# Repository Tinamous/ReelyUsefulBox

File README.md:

Reely Useful Box - SMD Reel storage and dispenser.
==================================================

SMD reel storage and dispenser based on a Really Useful Storage Box.

Each reel is held and dispensed individually.
The box will hold 25 individual reels (assuming standard 8mm tape for resistors/capacitors).
Each reel holder is 13mm wide. For wider tape/reels this could be doubled to keep to the same hole grid.
Each reel holder is made of 3 different printed parts (1x Top dispenser, 1x reel holder top, 2x reel arms).
Component counter option with LED and photodiode counting of the tape holes.

You can have as few as you want, or as many (well 25 per box and as many boxes as you need).

All design files are Openscad and .stl for direct printing. I found it best to print with a brim as these are long parts and have a tendency to warp at the ends.

##MountingPlate

This is the drilling guide. You can either print it out and drill, or laser cut some acrylic with it.

* Open the .svg file in Inkscape and print this out. 
* It's bigger than A4/Letter, do not scale it! (The box is bigger than A4 length ways so you will need a couple of these for the full 25 way box).
* Stick the sheet to the box lid, allow a margin of about 4mm around the edges where the lid inner curves up (remember the reel holder top has to fit inside).
* Ensure the holes line up with the Dispenser.
* Drill the holes. 
** 4MM for the M3 screw holes (4x).
** 5mm for the LED insert.
** 9-10mm for the square tape hole. This is likely to crack the lid in the process, maybe drill 4 M3.5 holes at each corner and cut, or cut out the entire length of all the sections with a dremel of something  (Be VERY careful if you use a knife, the lid is very tough!).

##Dispenser

This sits on the top of the lid. 

Print in any color you like, you can color code the dispensers to match your components. I'm using:

* 1206 Resistors: Red
* 0805 Resistors: Green
* 1206 Capacitors: White
* 0805 Capacitors: Grey
* 1206 LEDs (Blue): Blue
* Other: Bronze

Original inspiration taken from http://www.thingiverse.com/thing:1080195 with modifications.

* Print this on it's side without supports but with a brim.
* 4 mounting holes for M3 countersunk machine screws.
* A small hole that aligns with the holes in the tape and accepts a 3mm LED underneath.
* The tape film wraps around the block on the top and exits vertically, so pulling the tape film up advances the tape and removes the film.
* Of you can just leave the film on if you want to cut of a section of tape.
* The top block has a hold in the back. Use a M3 heatfit   insert in here if you want to use the component usage sensor block.

## ReelHolder-Top (ReelHolder.scad/ReelHolder.stl)

This sits inside the box to hold the reel arms and is screwed to the lid with the dispenser on the top.

* Print without supports but with a brim as this tends to warp at the edges.
* Fit 3x or 4x M3 HeatFit inserts (Do not fit the one by the square cut out if you wish to use the ComponentUsageSensor block.
* The M5 hole allows a 3mm LED to be pushed through into the dispenser 

## ReelHolder-Arm

These hold the reel and is mounted in the ReelHolder-Top.

* Print 2x of these for each arm.
* These push together either side of the reel and the ReelHolder-Top
* For the end ones you may wish to use a M3 HeatFit insert and small machine screw to hold the tops together if you don't have a tight fit.
* If the arms are not a good fit together change the value of cyinderMatingTollerance in the OpenScad file. I found 0.4 worked well, 0.2 was very tight.
* You may also like to shorten these arms. The variable armHeight sets the length of these. 150mm should allow the reel to be pulled to one side to be replaced.

## Parts Required:

* M3 Heatfit insert Part 1010655 http://www.insertsdirect.com/cgi-bin/sh000001.cgi?WD=1010655&PN=unheaded-heatfit-insert%2ehtml#a1010655
* M3 x 20mm countersunk machine screw (x5 per reel)
* M3 x 6mm countersunk machine screw (x1 for end reels only, or x2 per reel if you need to keep the reel arms together).
* 19XL Really Useful Box http://www.ryman.co.uk/really-useful-storage-box-19xl-litre
* PLA.
* Drills: 4mm, 5mm, 9 or 10mm.
* SMD devices on reels!

## Printer Settings

* Printer: Ultimaker 2 Extended+
* Print Sequence: One at a Time
* Profile: Fast print
** Layer Height: 0.15
** Infil: 20%
** Speed: 60 mm/s
** Wall Thickness: 0.7mm
** Top/Bottom Thickness: 0.75mm
* Build Plate Adhesion: Brim
* Support: None

## Electronics

The dispenser is designed to have a LED/PhotoTransistor pair either side of the tape to count the holes in the tape as they pass. See PCB folder for
instructions on the counter and LED PCB.

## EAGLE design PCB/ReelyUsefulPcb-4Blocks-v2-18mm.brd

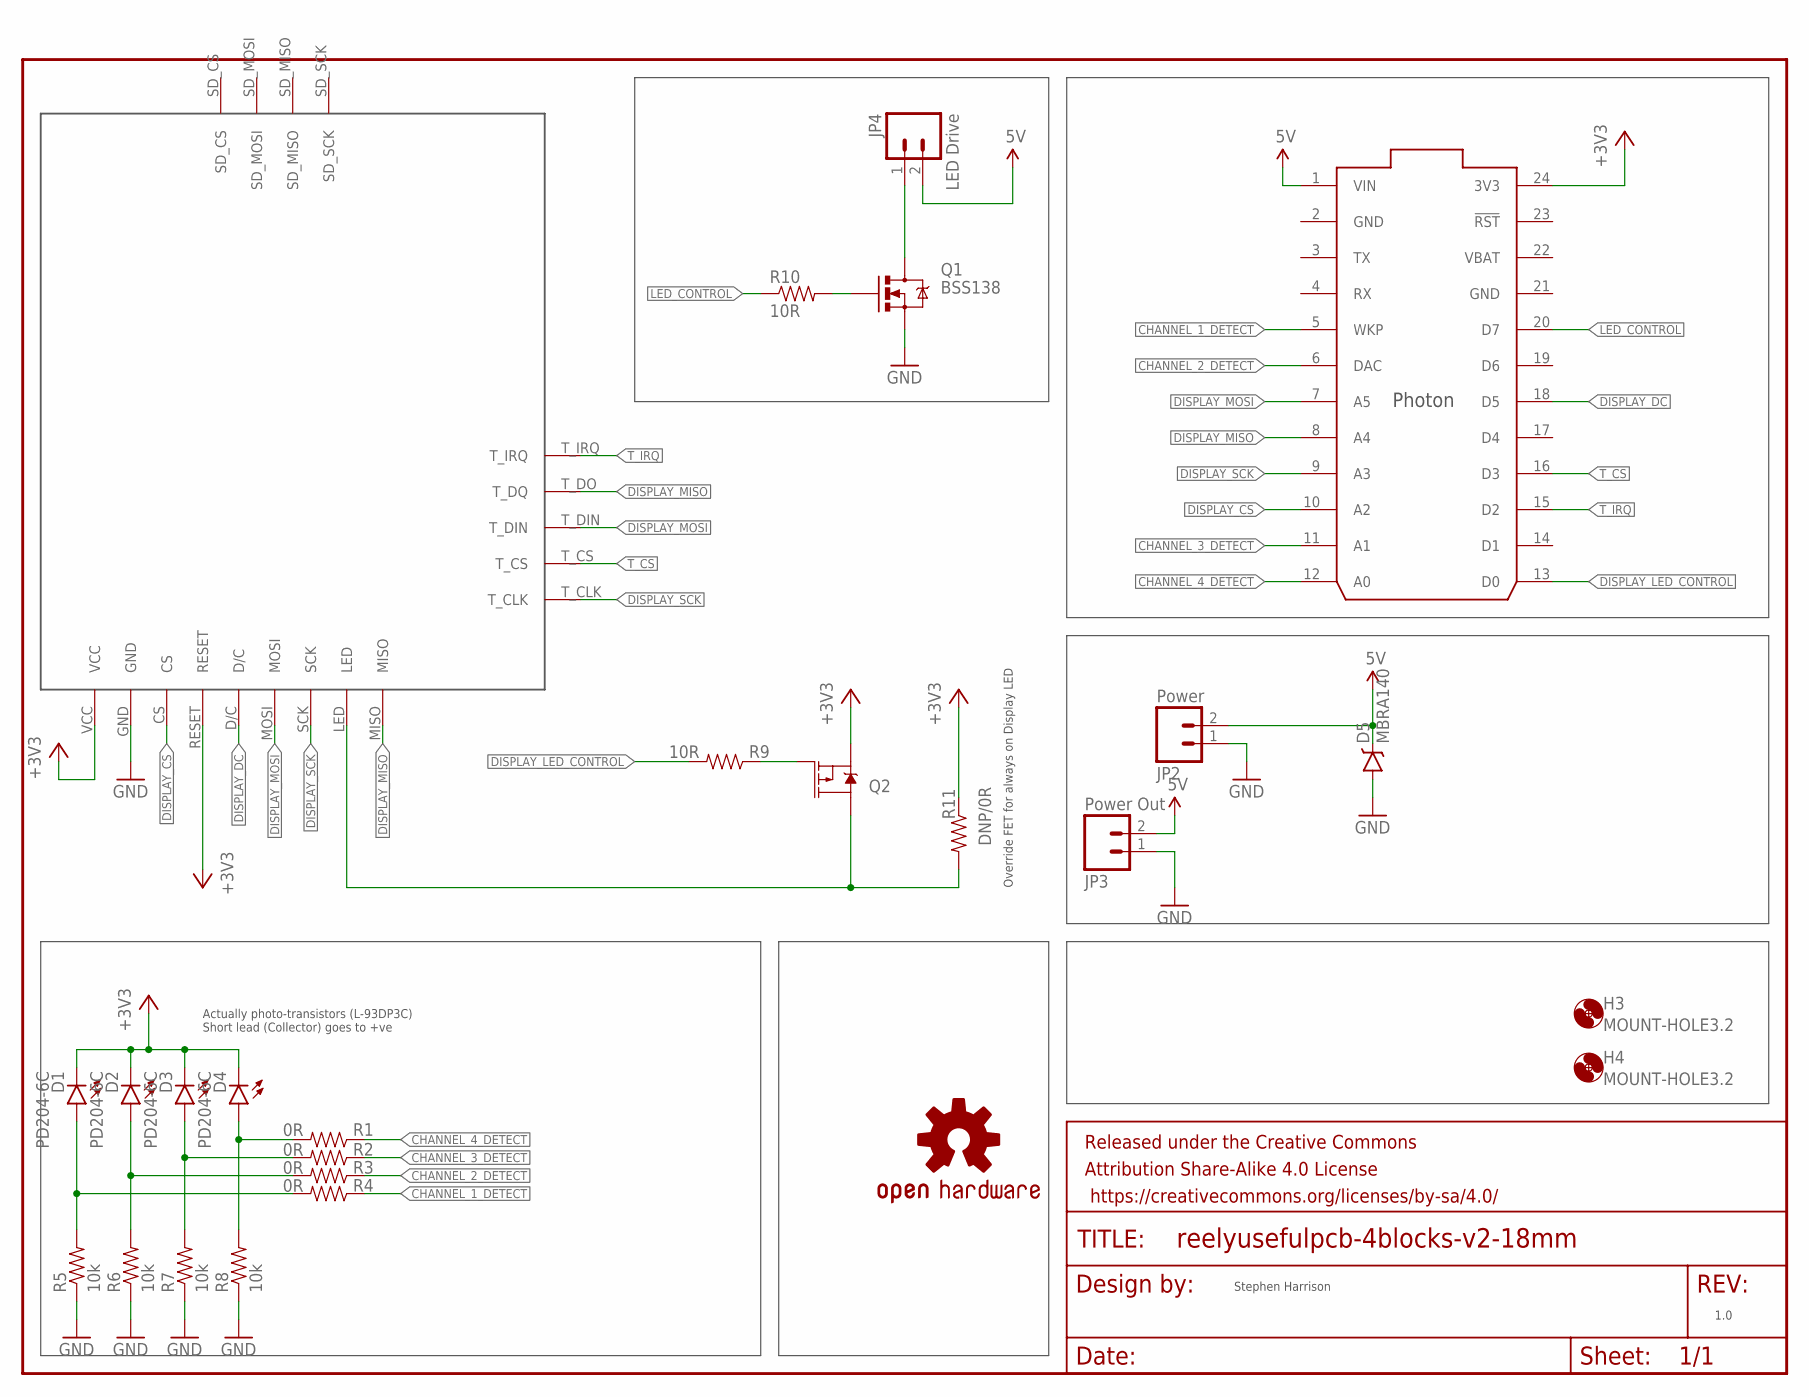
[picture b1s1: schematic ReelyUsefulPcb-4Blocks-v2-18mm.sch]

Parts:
D1, D2, D3, D4: PD204-6C; LED3MM
D5: MBRA140; SMA-DIODE
FRAME1: FRAME-LETTER; CREATIVE_COMMONS
H3, H4: MOUNT-HOLE3.2; 3,2
JP2: Power; JST-2-SMD
JP3: Power Out; JST-2-SMD
JP4: LED Drive; JST-2-SMD
LOGO1: OSHW-LOGOL; OSHW-LOGO-L
Q1: BSS138; SOT23-3@1; FARNELL 9845330
Q2: 2.5A/30V/105mΩ; SOT23-3
R1, R2, R3, R4: 0R; 1206
R5, R6, R7, R8: 10k; 1206
R9, R10: 10R; 1206
R11: DNP/0R; 1206
U2: TJCTM240NO-MOUNTING-HOMES; TJCTM240-NOHOLES
U3: PHOTON_SMD

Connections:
5V: D5.C, JP2.2 (1), JP3.2 (1), JP4.2 (1), U3.1 (VIN)
+3V3: D1.K (C), D2.K (C), D3.K (C), D4.K (C), Q2.2 (S), R11.1, U2.RESET, U2.VCC, U3.24 (3V3)
CHANNEL_1: D1.A, R4.2, R5.2
CHANNEL_1_DETECT: R4.1, U3.5 (WKP)
CHANNEL_2: D2.A, R3.2, R6.2
CHANNEL_2_DETECT: R3.1, U3.6 (DAC)
CHANNEL_3: D3.A, R2.2, R7.2
CHANNEL_3_DETECT: R2.1, U3.11 (A1)
CHANNEL_4: D4.A, R1.2, R8.2
CHANNEL_4_DETECT: R1.1, U3.12 (A0)
DISPLAY_CS: U2.CS, U3.10 (A2)
DISPLAY_DC: U2.D/C, U3.18 (D5)
DISPLAY_LED_CONTROL: R9.2, U3.13 (D0)
DISPLAY_MISO: U2.MISO, U2.T_DO (T_DQ), U3.8 (A4)
DISPLAY_MOSI: U2.MOSI, U2.T_DIN, U3.7 (A5)
DISPLAY_SCK: U2.SCK, U2.T_CLK, U3.9 (A3)
GND: D5.A, JP2.1 (2), JP3.1 (2), Q1.2 (S), R5.1, R6.1, R7.1, R8.1, U2.GND, U3.2 (GND), U3.21 (GND)
LED_CONTROL: R10.1, U3.20 (D7)
unnamed: JP4.1 (2), Q1.3 (D)
unnamed: Q2.1 (G), R9.1
unnamed: Q1.1 (G), R10.2
unnamed: Q2.3 (D), R11.2, U2.LED
T_CS: U2.T_CS, U3.16 (D3)
T_IRQ: U2.T_IRQ, U3.15 (D2)
VBAT: U3.22 (VBAT)

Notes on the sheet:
Actually photo-transistors (L-93DP3C) Short lead (Collector) goes to +ve
1.0
Stephen Harrison
Override FET for always on Display LED

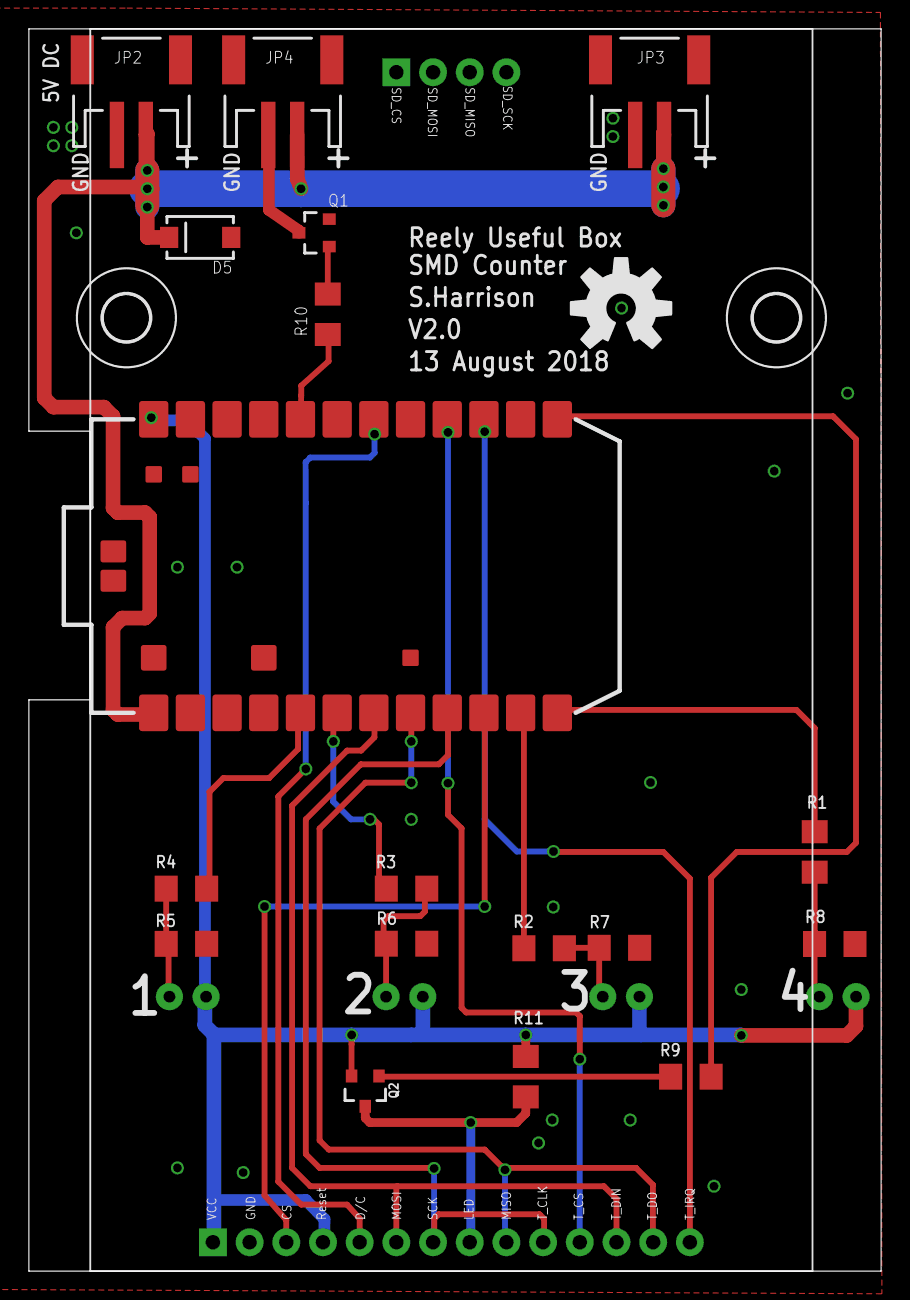
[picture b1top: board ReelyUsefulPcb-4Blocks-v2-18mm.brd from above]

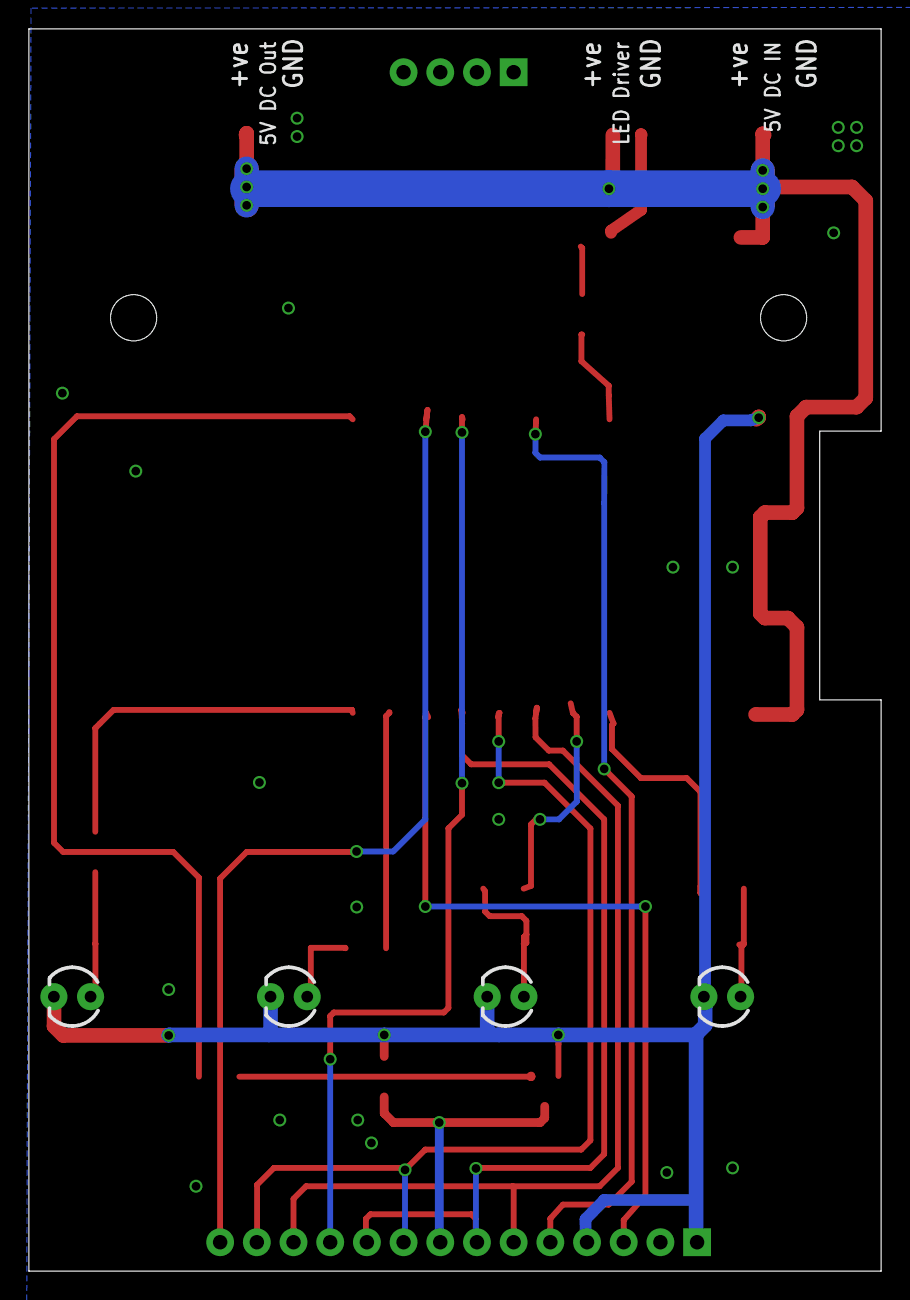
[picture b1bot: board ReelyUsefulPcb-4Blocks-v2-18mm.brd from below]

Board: 2 copper layers, 59.0 x 86.0 mm, 27 parts (4 on the bottom side), 24 nets.

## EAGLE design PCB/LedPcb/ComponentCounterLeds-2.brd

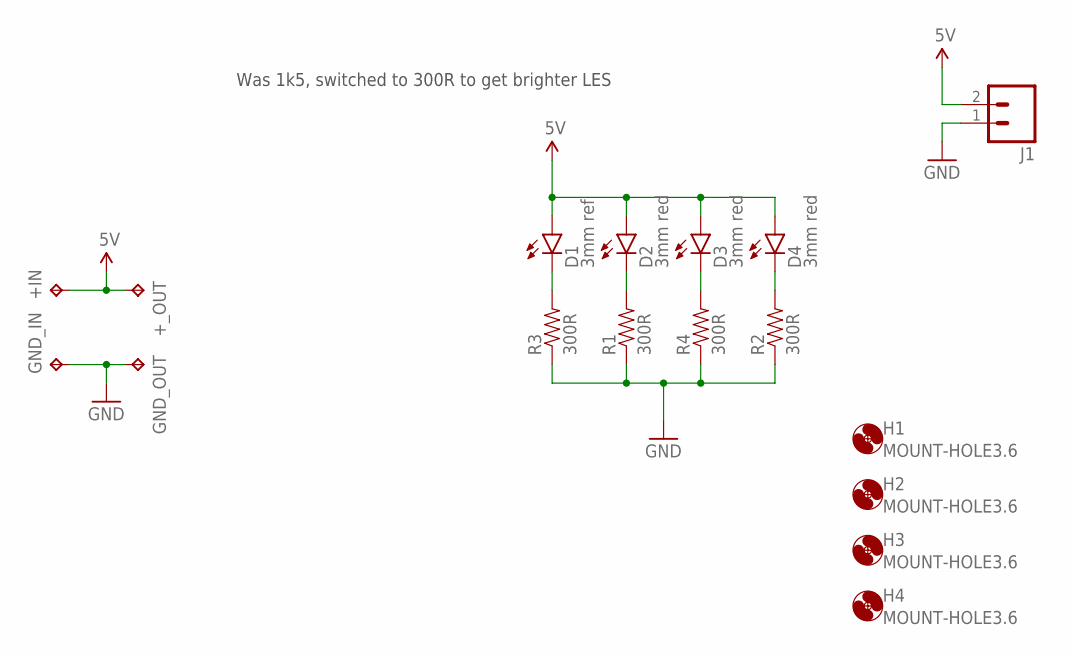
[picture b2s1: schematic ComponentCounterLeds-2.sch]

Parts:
+IN: TPTP15R; TP15R
+_OUT: TPTP15R; TP15R
D1: 3mm ref; LED3MM-NS
D2, D3, D4: 3mm red; LED3MM-NS
GND_IN: TPTP15R; TP15R
GND_OUT: TPTP15R; TP15R
H1, H2, H3, H4: MOUNT-HOLE3.6; 3,6
J1: M02-JST-2MM-SMT; JST-2-SMD; FARNELL 9492615
R1, R2, R3, R4: 300R; 1206

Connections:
5V: +IN.TP, +_OUT.TP, D1.A, D2.A, D3.A, D4.A, J1.2 (1)
GND: GND_IN.TP, GND_OUT.TP, J1.1 (2), R1.1, R2.1, R3.1, R4.1
unnamed: D2.K (C), R1.2
unnamed: D4.K (C), R2.2
unnamed: D3.K (C), R4.2
unnamed: D1.K (C), R3.2

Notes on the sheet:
Was 1k5, switched to 300R to get brighter LES

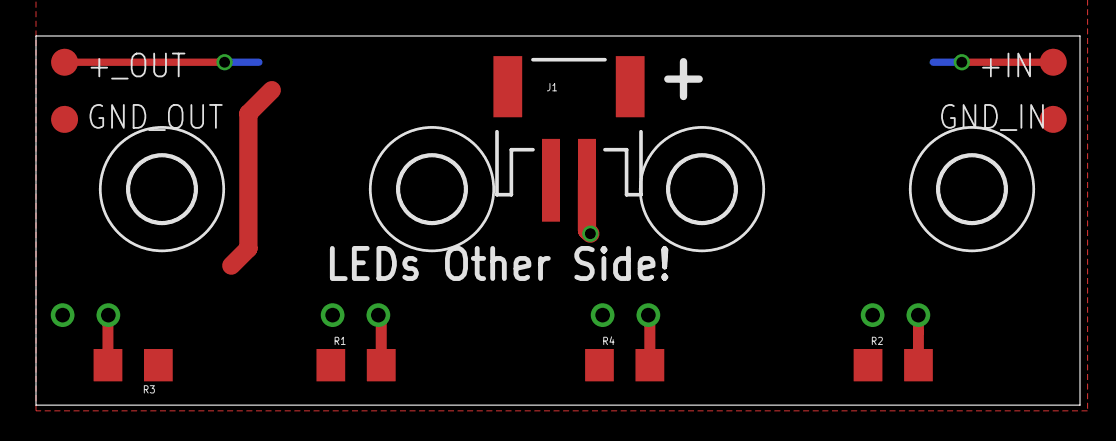
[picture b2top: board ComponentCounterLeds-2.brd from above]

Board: 2 copper layers, 58.0 x 20.5 mm, 17 parts (0 on the bottom side), 6 nets.

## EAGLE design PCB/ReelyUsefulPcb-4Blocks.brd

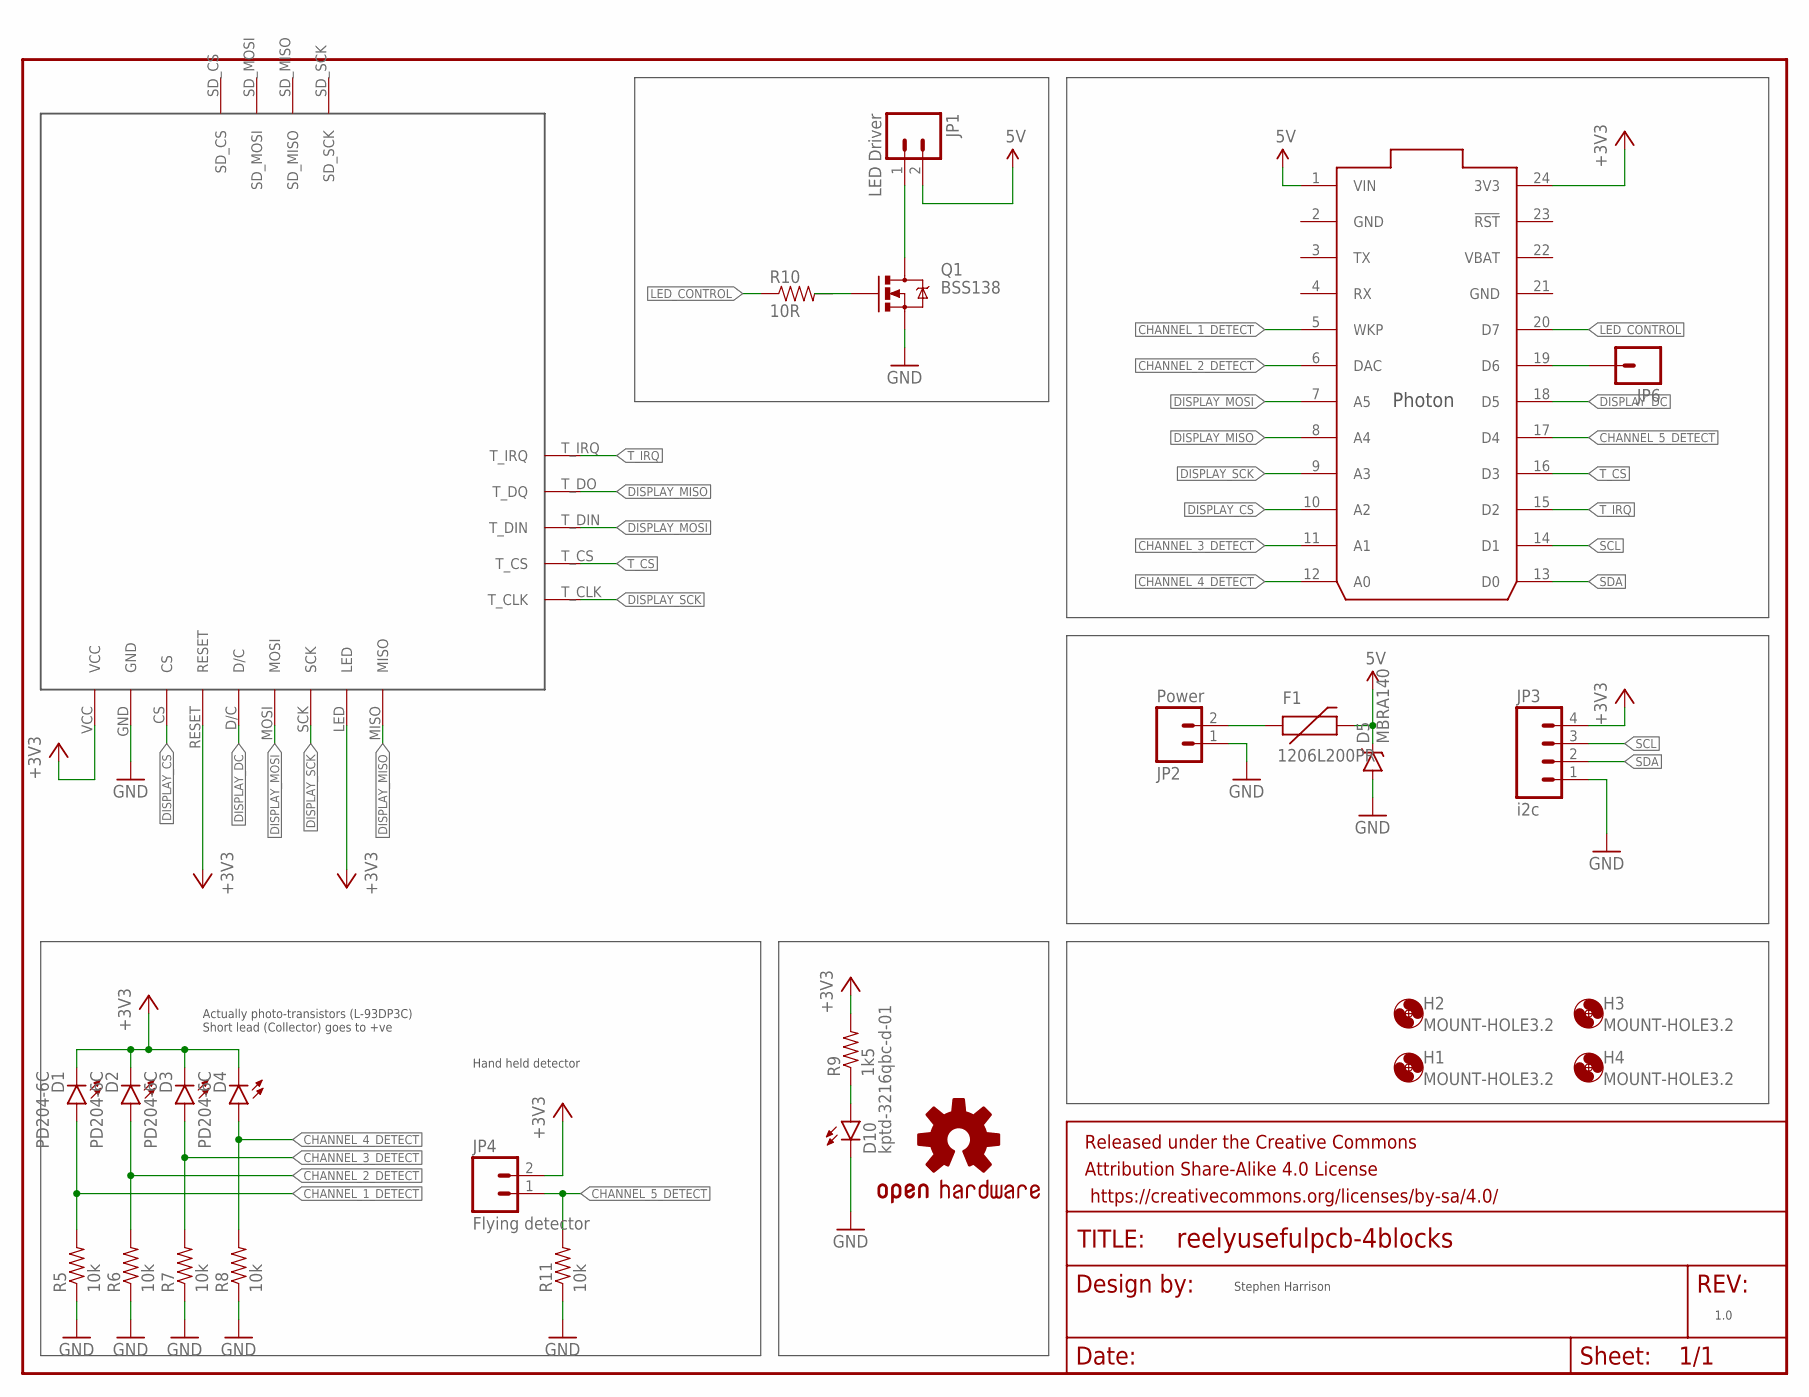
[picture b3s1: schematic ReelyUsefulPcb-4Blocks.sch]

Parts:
D1, D2, D3, D4: PD204-6C; LED3MM
D5: MBRA140; SMA-DIODE
D10: kptd-3216qbc-d-01; LED-1206-BOTTOM; FARNELL 2290349
F1: 1206L200PR; PTC-1206; FARNELL 2383297
FRAME1: FRAME-LETTER; CREATIVE_COMMONS
H1, H2, H3, H4: MOUNT-HOLE3.2; 3,2
JP1: LED Driver; JST-2-PTH
JP2: Power; JST-2-SMD
JP3: i2c; 1X04
JP4: Flying detector; JST-2-PTH
JP6: M01PTH; 1X01
LOGO1: OSHW-LOGOL; OSHW-LOGO-L
Q1: BSS138; SOT23-3; FARNELL 9845330
R5, R6, R7, R8, R11: 10k; 1206
R9: 1k5; 1206
R10: 10R; 1206
U2: TJCTM240
U3: PHOTON_SMD

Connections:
5V: D5.C, F1.2, JP1.2, U3.1 (VIN)
+3V3: D1.K (C), D2.K (C), D3.K (C), D4.K (C), JP3.4, JP4.2, R9.2, U2.LED, U2.RESET, U2.VCC, U3.24 (3V3)
CHANNEL_1_DETECT: D1.A, R5.2, U3.5 (WKP)
CHANNEL_2_DETECT: D2.A, R6.2, U3.6 (DAC)
CHANNEL_3_DETECT: D3.A, R7.2, U3.11 (A1)
CHANNEL_4_DETECT: D4.A, R8.2, U3.12 (A0)
CHANNEL_5_DETECT: JP4.1, R11.2, U3.17 (D4)
DISPLAY_CS: U2.CS, U3.10 (A2)
DISPLAY_DC: U2.D/C, U3.18 (D5)
DISPLAY_MISO: U2.MISO, U2.T_DO (T_DQ), U3.8 (A4)
DISPLAY_MOSI: U2.MOSI, U2.T_DIN, U3.7 (A5)
DISPLAY_SCK: U2.SCK, U2.T_CLK, U3.9 (A3)
GND: D5.A, D10.C, JP2.1 (2), JP3.1, Q1.2 (S), R5.1, R6.1, R7.1, R8.1, R11.1, U2.GND, U3.2 (GND), U3.21 (GND)
LED_CONTROL: R10.1, U3.20 (D7)
unnamed: D10.A, R9.1
unnamed: JP1.1, Q1.3 (D)
unnamed: JP6.1, U3.19 (D6)
unnamed: Q1.1 (G), R10.2
unnamed: F1.1, JP2.2 (1)
SCL: JP3.3, U3.14 (D1)
SDA: JP3.2, U3.13 (D0)
T_CS: U2.T_CS, U3.16 (D3)
T_IRQ: U2.T_IRQ, U3.15 (D2)
VBAT: U3.22 (VBAT)

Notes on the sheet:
Hand held detector
Actually photo-transistors (L-93DP3C) Short lead (Collector) goes to +ve
1.0
Stephen Harrison

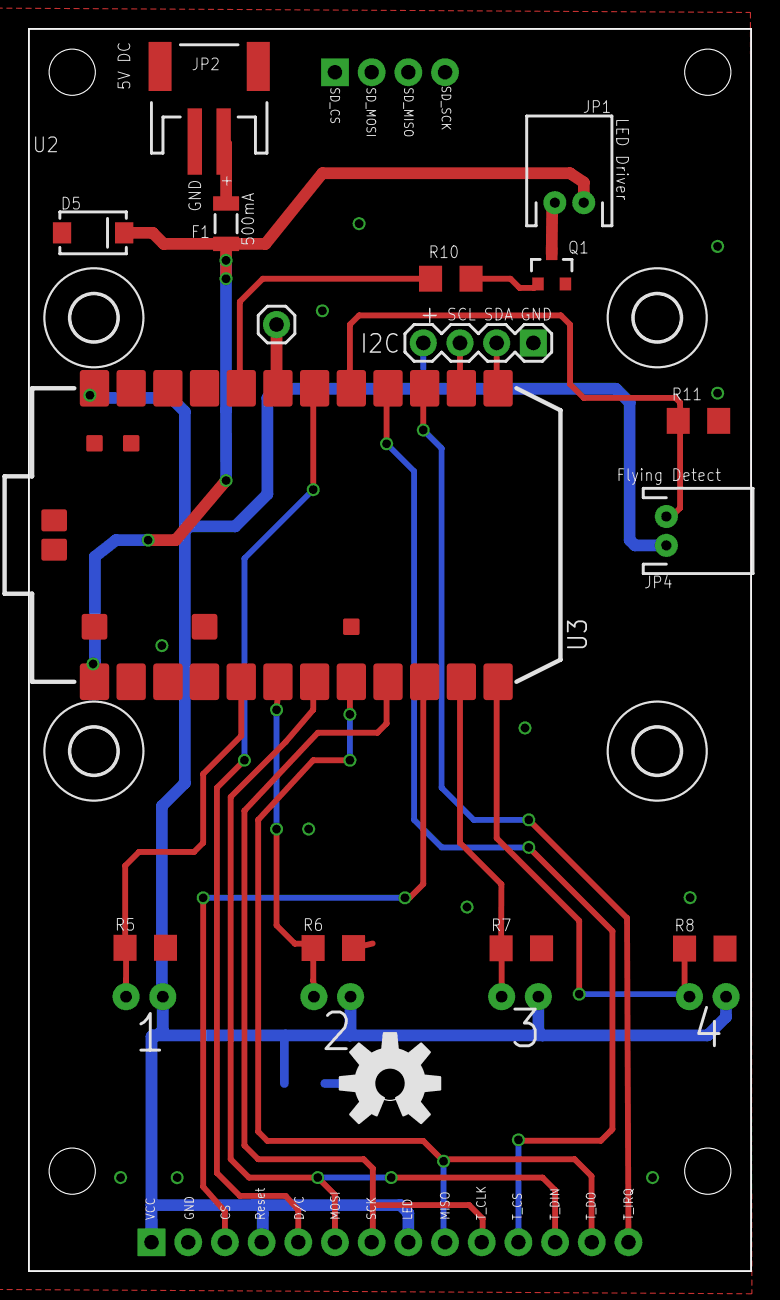
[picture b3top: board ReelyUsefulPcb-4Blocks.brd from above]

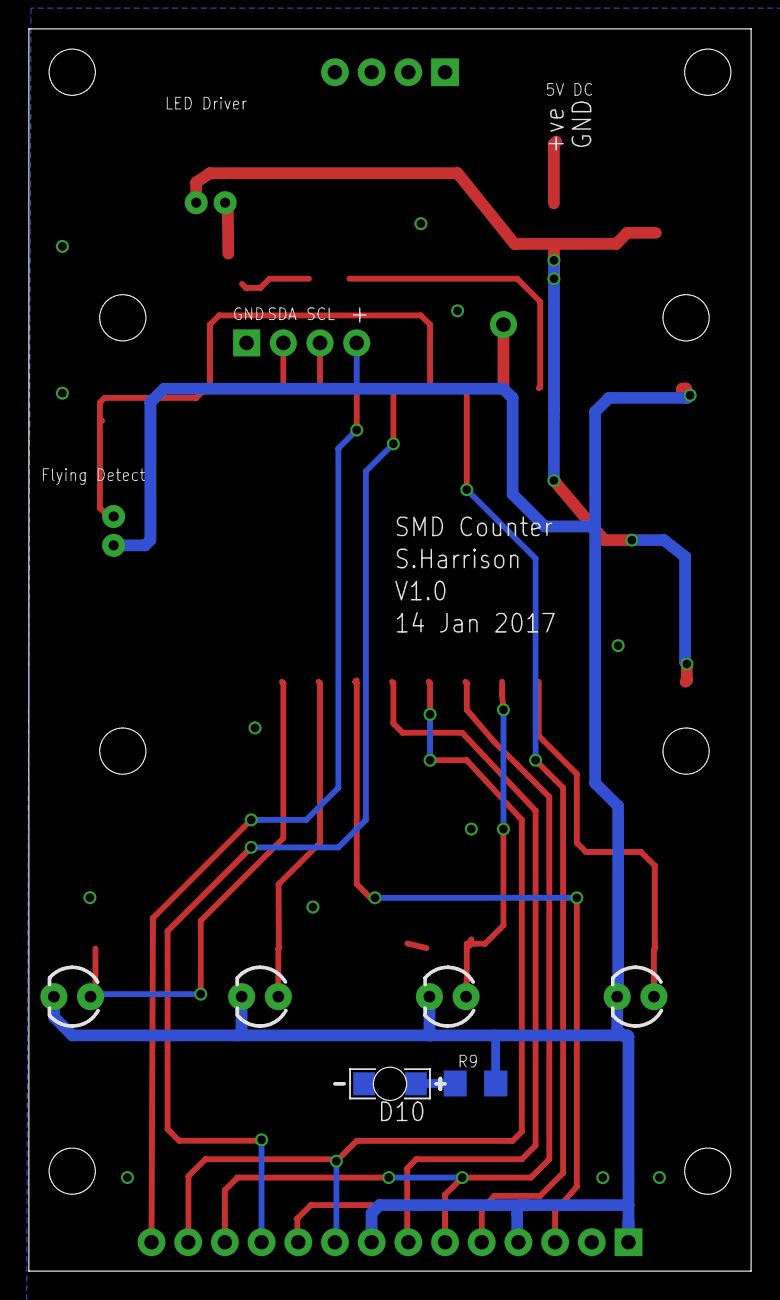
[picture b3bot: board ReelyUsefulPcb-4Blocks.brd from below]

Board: 2 copper layers, 50.0 x 86.0 mm, 28 parts (6 on the bottom side), 23 nets.

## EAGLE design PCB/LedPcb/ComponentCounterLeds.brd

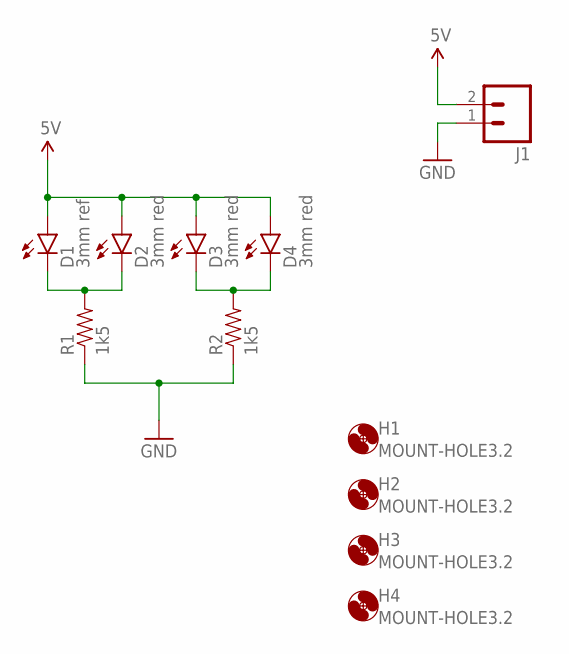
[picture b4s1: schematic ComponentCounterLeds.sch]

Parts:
D1: 3mm ref; LED3MM-NS
D2, D3, D4: 3mm red; LED3MM-NS
H1, H2, H3, H4: MOUNT-HOLE3.2; 3,2
J1: M02-JST-2MM-SMT; JST-2-SMD; FARNELL 9492615
R1, R2: 1k5; 1206

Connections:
5V: D1.A, D2.A, D3.A, D4.A, J1.2 (1)
GND: J1.1 (2), R1.1, R2.1
unnamed: D1.K (C), D2.K (C), R1.2
unnamed: D3.K (C), D4.K (C), R2.2

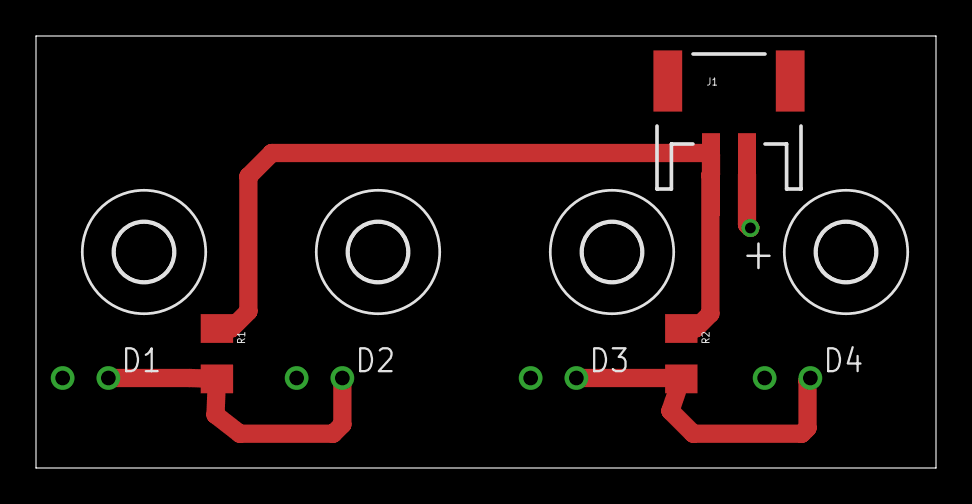
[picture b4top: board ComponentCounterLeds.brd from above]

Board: 2 copper layers, 50.0 x 24.0 mm, 11 parts (0 on the bottom side), 4 nets.

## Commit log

2017-01-11 Work in progress initial version of SMD Reel holder.
2017-01-11 Removed material so that the riser arm can fit either side of the base.
2017-01-11 Made the LED hole a little smaller so the LED would fit snugly.
2017-01-12 Added more places to the mounting plate.
2017-01-12 Made the enterance cutout bigger to make it easier to feed the tape in.
    Changed exit cutout so it's actually a ramp so that the tape is pushed over the edge of the lid.
2017-01-12 Increased the tollerance for the mating cylinder fits as 0.2 was tight and difficult to seperate.
    Renamed riser... to arm... as it better represents what it is.
2017-01-12 Added previous version of reel holders into Alternative folder.
2017-01-12 Added stl files.
2017-01-12 Renamed SMDReallyUsefulDispenser to Dispenser and ReelHolder2 to ReelHolder.
2017-01-12 Added readme.
2017-01-12 Added photos.
2017-01-12 Updated readme. Added Printer Settings.
2017-01-12 Added color coding of dispenser.
    Added image at the head.
    Changed H1's to be H2's for the sub sections.
2017-01-12 Set to 25 reels (blocks).
2017-01-12 Spelling fixes.
2017-01-14 Started to move common values out into its own Common.scad file.
    Changed tape height for counter block to slightly less than the enterance to the block on the dispenser.
    Shortened length to match change with new dispenser and so it's just longer than the display PCB.
    Improved screw holes.
2017-01-15 Moved film removal block back a bit to fit the Counter PCB better and made it longer to allow for labeling to fit on it easily.
    Updated to use the Common.scad file for shared common values.
    Tidied up the code a bit.
    Changed screw hole #3 to allow for a hidden screw head underneath so that the arm top may be held in position by a screw and the dispencer removed.
2017-01-15 Split ReelHolder to ReelHolder and ReelHolderArm files and updated stl's to match.
    Changed screw holes to support holding M3 nuts also so that the HeatFit inserts are not required for the reel holder top.
    Changed screw hole (well nut holder) to be deeper than the others as the screw has to go through the top component block as well and it's a long distance for a M3 screw.
2017-01-15 Changed width to split out the actual desired spacing with and the printer tollerance allowance.
2017-01-15 Reduced height as much as possible as it's going to be fairly tall with the display on.
2017-01-15 Rebuild all the stls
    Added Build.bat to build all the stl's in one go.
2017-01-24 Fixed typo.
    Updated the colours/quantity I'm using
2017-01-24 Fixed tape wall width and the overall width.
    Removed dead code.
2017-01-24 Rebuilt from scad file
2017-01-24 Added PCB design for component counter add-on.
    *** Untested ***
    As sent to DirtyPCBs.
2017-01-24 Fixed some sizing issues.
2017-01-24 Added ability to use a pin to connect to the dispenser rather than screw as this works well when SLA printed.
2017-01-24 Updated tollerance for printing nad added tape hole offset.
2017-01-24 Changed component sensor build for the pin version.
2017-01-24 Another typo fix.
2017-01-24 Another typo.
2017-01-28 Reduced printer tollerance gap slightly.
    Increased gap in cylinder mating for the reel holder arm.
    rebuilt stl's.
2017-01-30 Added numberOfBlocksWide to specify how many units of block width (13mm) the arm/reel holder/dispencer/component counter should be to allow for wide tape (LEDs etc).
2017-01-30 Rounded the edge of the tape enterance and added box that should sit inside the lid lip to give a nicer finish.
    Added numberOfBlocksWide to specify how many units of block width (13mm)
    Modified m3/pin from component sensor holes so they stay at a fixed Z and do not move with tape height.
2017-01-30 Set to use common values rather than having it's own block width.
    Modified to support multi-block width reel holder and kept contact area to small size.
2017-01-30 Added support for multiple block width.
    Added curve to tape enterance to stop LED tape snagging.
2017-01-30 Added support for multi-block and tapeWidth.
    It might be wide tape (e.g. 12mm LED) which needs 2 blocks but the tape needs to be kept with the correct path.
2017-01-30 Added builds for multi-block width units.
2017-01-30 Added repetition for LED hole to multi-block width as they can be used for drill tempate and possibly a PCB underneath to hold the LEDs in the future.
2017-01-30 Reduced size for tape feed enterance and made the marker optional with the curve to the enterance always.
2017-01-30 Restored to 1 block wide by default.
2017-01-30 Added LED holes for multiblock widths so that if a PCB is used to insert the LEDs then holes still exist for the led to align into.
2017-01-30 rebuild stls
2017-02-14 Updated build to include a LED tape dispencer with larger gap.
2017-05-09 Updated notes.
2017-05-09 Added gitignore to ignore all the junk Eagle files.
2017-05-09 Added the LED PCB.
2017-05-09 Adding dimensions "datasheet" for the display used.
2017-05-09 Added datasheet for phototransistor used.
2017-05-22 Refacotred the arm so that the coordinates make more sense.
    Dropped width to 1mm as 2mm is a bit to big with the reels fitted.
2017-05-22 Improved readme
2017-05-22 Improved component sensor to allow a nut to be inserted horizontally for fixing the PCB otherwise the nut needs to be in before this is screwed to the case which is difficult.
    Opneed up more space on the board to allow for pins.
2017-08-17 Rebuilt stls. made arm thinner as it is a little too wide and causes the reels to be larger than their allowed area.
    Improvements in dispenser for multi block width units.
2017-08-17 Monior improvements to pcb/schematic names and values.
2017-08-17 Added case for the display unit.
2017-08-17 Work in progress component catcher
2017-08-17 Added ComponentCatcher to build.bat file.
    Created stl for component catcher.
2018-10-01 Changed each spool block width to 15mm to give more space for the spools.
2018-10-01 Backup of old 13mm wide version.

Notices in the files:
parts and their libraries:
SparkFun-LED: Licensing: Creative Commons ShareAlike 4.0 International - https://creativecommons.org/licenses/by-sa/4.0
SparkFun-Aesthetics: Released under the Creative Commons Attribution Share-Alike 4.0 License
SparkFun-Aesthetics: https://creativecommons.org/licenses/by-sa/4.0
